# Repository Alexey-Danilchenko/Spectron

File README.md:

# Spectron

Spectron - an open source project for measuring and obtaining digital devices spectral sensitivity curves

Copyright (C) 2014-Now [Alexey Danilchenko](mailto:alexey.danilchenko@gmail.com), [Iliah Borg](mailto:iliah.i.borg@gmail.com)

*This is a work in progress*

# Introduction

This is the second generation of the open source Spectron project.  Initially this was conceived with the goal of constructing an automated device with an aid to accurately measure spectral sensitivity curves for digital camera sensors. The project has a broader use though and can be used to measure spectral sensitivity curves of various light sensitive sensors (not just camera sensors) - for example spectral sensitivity curves of photodiodes.

The main goal however is still to aid measurement of spectral sensitivity of digital cameras sensors and this is what this project and documentation will be aimed towards. For more details on the application of that and the ultimate reasons _why_ please [read this](CameraSRF.md).

The second generation of Spectron board was produced with the more accurate spectral readings in mind, better analogue circuitry to drive Hamamatsu spectrometers and more stable measurement results.

# Concept

The spectral sensitivity measurements of a selected device are fairly simple in principle:

1. broadband light source of high intensity is passed via monochromator
2. monochromator output is fed to the integrating sphere 
3. integrating sphere output is simultaneously captured by target device and measured spectrally
4. steps 1-3 repeated through selected spectral range in discrete steps (5nm steps over 380-720nm range for example)
5. the results of measurements from target device are scaled accodringly to the spectra of the light measured at each step and target spectral sensitivity curves are produced

# Hardware

The hardware for the above concept consists of the light source (LED or pulsed  Xenon), Mini-Chrom MC1-02 monochromator, 2.5" integrating sphere and several distinct components. The Spectrometer component is a hardware driving Hamamatsu [C12666MA](http://www.hamamatsu.com/jp/en/C12666MA.html) or [C12880MA](http://www.hamamatsu.com/jp/en/C12880MA.html) spectrometer sensor to capture spectral readings from the integrating sphere and initiate synchronised readings from target device. The Stepper Motors component is a hardware for automating monochromator operation (esentially converting manually controlled monochromator to scanning monochromator, turning broadband light source into tunable source). The Light Source component is a hardware for controlling broadband light source that provides input for the monochromator.

With the precise intensity control of the LED light source, the whole system is essentially providing tunable monochromatic light source covering the entire visible range.

All hardware component boards use [Particle Photon controllers](https://docs.particle.io/datasheets/wi-fi/photon-datasheet/) at their core to drive the functionality. Overall application control is performed from Windows/Mac application running on a computer operating the boards via Particle or local cloud (the latter is more responsive).

Boards used for all individual components can be of course utilised for standalone projects - see corresponding sections for details.

For more details please refer to individual parts of the project below:

* [Firmware](firmware) - [Particle Photon](https://www.particle.io/products/hardware/photon-wifi-dev-kit) code running on the boards
* [Hardware](hardware) - boards, schematics (Eagle) and BOM 
* [Software](software) - Windows/MacOS X application controlling the overall functionality

# Open Source

This project is open source software and hardware and is released under:

* [GNU General Public License v3](https://www.gnu.org/licenses/gpl-3.0.en.html) for the software parts and 
* [CERN Open Hardware Licence]( http://www.ohwr.org/attachments/735/CERNOHLv1_1.txt) for hardware parts

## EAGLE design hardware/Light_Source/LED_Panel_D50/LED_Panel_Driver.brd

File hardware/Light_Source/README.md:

# Light Sources

The Spectron 2 project uses a wideband light source component as an input to the monochromator. Several light sources with full visible spectrum coverage were evaluated, built and tested for this project. It is important to realize that flat spectrum is not necessary in this application. What is required from a light source is a continuous spectrum, with no gaps. Evaluated light sources all satisfy this criteria. Below is the list of the light sources chosen as a result of this evaluation:

* [LED light source](LEDs) - greater stability and control, this is the preferred light source for Spectron 2 project.
* [Pulsed Xenon short arc light source](Xenon) - great visible spectrum coverage, compact package and point light source best suited to guide light to the monochromator.

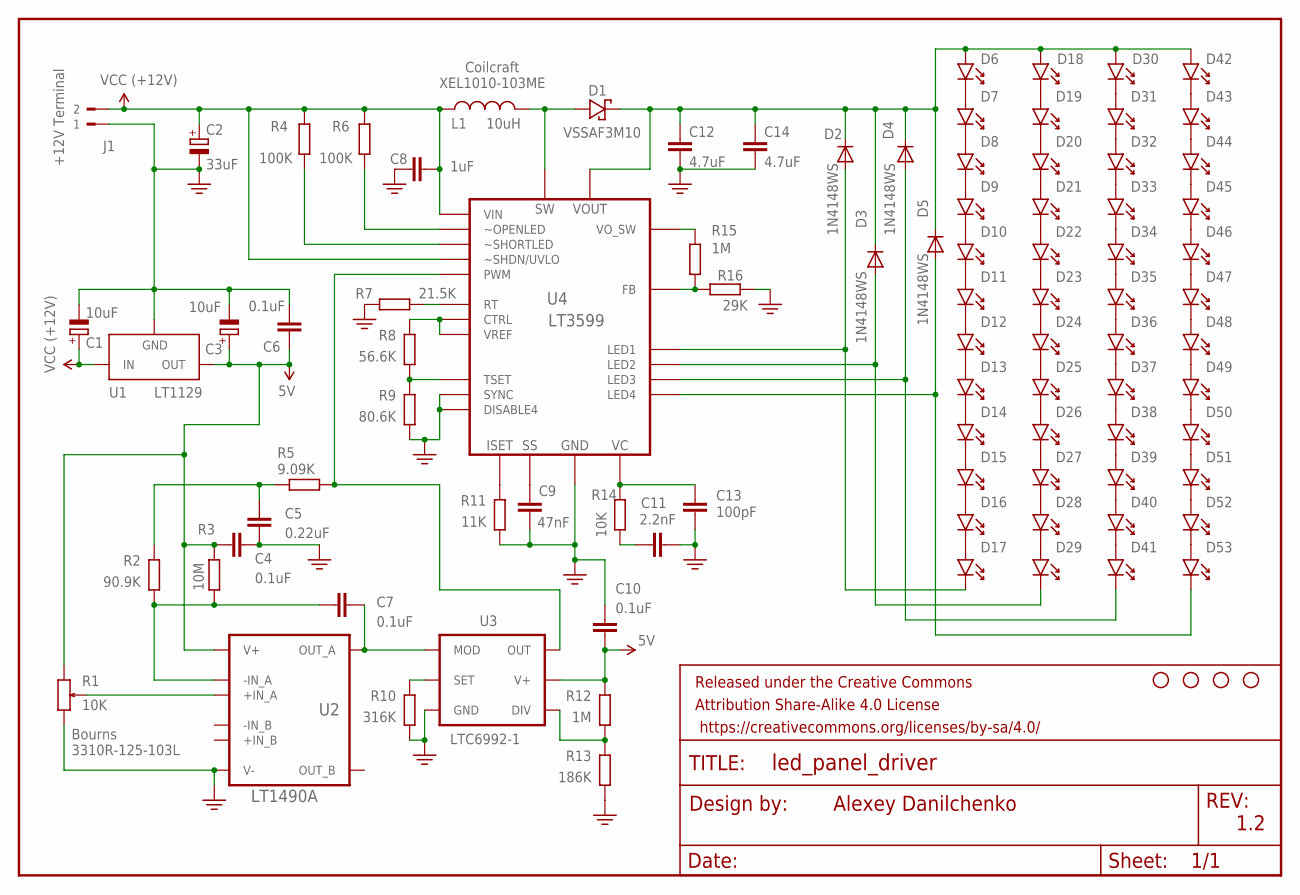
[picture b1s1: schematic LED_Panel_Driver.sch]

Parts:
C1, C3: 10uF; CT7343
C2: 33uF; PANASONIC_E
C4, C6, C7, C10: 0.1uF; C0805
C5: 0.22uF; C0805
C8: 1uF; C0805
C9: 47nF; C0805
C11: 2.2nF; C0805
C12, C14: 4.7uF; C1812
C13: 100pF; C0805
D1: VSSAF3M10; SODFL5226X100N
D2, D3, D4, D5: 1N4148WS; SOD-323F
D6, D7, D8, D9, D10, D11, D12, D13, D14, D15, D16, D17, D18, D19, D20, D21, D22, D23, D24, D25, D26, D27, D28, D29, D30, D31, D32, D33, D34, D35, D36, D37, D38, D39, D40, D41, D42, D43, D44, D45, D46, D47, D48, D49, D50, D51, D52, D53: YUJI_D50
FRAME1: FRAME-LEDGER; CREATIVE_COMMONS
J1: +12V Terminal; WEIDMULLER_PM5.08_2
L1: 10uH; XAL1010
R1: 10K; 3310R125103L
R2: 90.9K; R0805
R3: 10M; R0805
R4, R6: 100K; R0805
R5: 9.09K; R0805
R7: 21.5K; R0805
R8: 56.6K; R0805
R9: 80.6K; R0805
R10: 316K; R0805
R11: 11K; R0805
R12, R15: 1M; R0805
R13: 186K; R0805
R14: 10K; R0805
R16: 29K; R0805
STANDOFF1, STANDOFF2, STANDOFF3, STANDOFF4: STAND-OFF
U1: LT1129; SOT223
U2: LT1490A; SOIC127P600X175-8N
U3: LTC6992-1; SOT95P280X100-6N
U4: LT3599; SOP65P640X120-29N

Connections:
5V: C3.+, C4.2, C6.1, C10.1, R1.3 (CCW), R3.1, R12.1, U1.3 (OUT), U2.8 (V+), U3.5 (V+)
GND: C1.-, C2.-, C3.-, C4.1, C5.1, C6.2, C8.2, C9.2, C10.2, C11.2, C12.2, C13.2, C14.2, J1.1, R1.1 (CW), R7.2, R9.2, R10.2, R11.2, R13.2, R16.1, U1.2 (GND), U1.4 (GND), U2.4 (V-), U3.2 (GND), U4.8 (DISABLE4), U4.19 (SYNC), U4.25 (GND), U4.29 (GND)
unnamed: R8.2, R9.1, U4.17 (TSET)
unnamed: D1.2 (A), L1.2, U4.1 (SW)
unnamed: C12.1, C14.1, D1.1 (K), D2.C, D3.C, D4.C, D5.C, D6.ANODE, D18.ANODE, D30.ANODE, D42.ANODE, U4.2 (VOUT)
unnamed: R15.1, R16.2, U4.16 (FB)
unnamed: D22.CATHODE, D23.ANODE
unnamed: D46.CATHODE, D47.ANODE
unnamed: D2.A, D17.CATHODE, U4.4 (LED1)
unnamed: R8.1, U4.14 (CTRL), U4.24 (VREF)
unnamed: D6.CATHODE, D7.ANODE
unnamed: D3.A, D29.CATHODE, U4.5 (LED2)
unnamed: C9.1, U4.23 (SS)
unnamed: R15.2, U4.3 (VO_SW)
unnamed: R11.1, U4.13 (ISET)
unnamed: R7.1, U4.22 (RT)
unnamed: C13.1, R14.2, U4.15 (VC)
unnamed: C11.1, R14.1
unnamed: R6.2, U4.11 (~OPENLED)
unnamed: R4.2, U4.9 (~SHORTLED)
unnamed: D7.CATHODE, D8.ANODE
unnamed: D8.CATHODE, D9.ANODE
unnamed: D9.CATHODE, D10.ANODE
unnamed: D11.CATHODE, D12.ANODE
unnamed: D12.CATHODE, D13.ANODE
unnamed: D13.CATHODE, D14.ANODE
unnamed: D14.CATHODE, D15.ANODE
unnamed: D15.CATHODE, D16.ANODE
unnamed: D16.CATHODE, D17.ANODE
unnamed: D10.CATHODE, D11.ANODE
unnamed: D18.CATHODE, D19.ANODE
unnamed: D19.CATHODE, D20.ANODE
unnamed: D20.CATHODE, D21.ANODE
unnamed: D21.CATHODE, D22.ANODE
unnamed: D23.CATHODE, D24.ANODE
unnamed: D24.CATHODE, D25.ANODE
unnamed: D25.CATHODE, D26.ANODE
unnamed: D26.CATHODE, D27.ANODE
unnamed: D27.CATHODE, D28.ANODE
unnamed: D28.CATHODE, D29.ANODE
unnamed: D30.CATHODE, D31.ANODE
unnamed: D31.CATHODE, D32.ANODE
unnamed: D32.CATHODE, D33.ANODE
unnamed: D33.CATHODE, D34.ANODE
unnamed: D35.CATHODE, D36.ANODE
unnamed: D36.CATHODE, D37.ANODE
unnamed: D37.CATHODE, D38.ANODE
unnamed: D38.CATHODE, D39.ANODE
unnamed: D39.CATHODE, D40.ANODE
unnamed: D40.CATHODE, D41.ANODE
unnamed: D34.CATHODE, D35.ANODE
unnamed: D42.CATHODE, D43.ANODE
unnamed: D43.CATHODE, D44.ANODE
unnamed: D44.CATHODE, D45.ANODE
unnamed: D45.CATHODE, D46.ANODE
unnamed: D47.CATHODE, D48.ANODE
unnamed: D48.CATHODE, D49.ANODE
unnamed: D49.CATHODE, D50.ANODE
unnamed: D50.CATHODE, D51.ANODE
unnamed: D51.CATHODE, D52.ANODE
unnamed: D52.CATHODE, D53.ANODE
unnamed: D4.A, D41.CATHODE, U4.6 (LED3)
unnamed: D5.A, D53.CATHODE, U4.7 (LED4)
unnamed: R10.1, U3.3 (SET)
unnamed: C7.2, R2.2, R3.2, U2.2 (-IN_A)
unnamed: C7.1, U2.1 (OUT_A), U3.1 (MOD)
unnamed: R5.1, U3.6 (OUT), U4.21 (PWM)
unnamed: R1.2 (WIPER), U2.3 (+IN_A)
unnamed: R12.2, R13.1, U3.4 (DIV)
unnamed: C5.2, R2.1, R5.2
VDD: C1.+, C2.+, C8.1, J1.2, L1.1, R4.1, R6.1, U1.1 (IN), U4.27 (~SHDN/UVLO), U4.28 (VIN)

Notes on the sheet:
1.2
Coilcraft XEL1010-103ME
Alexey Danilchenko
Bourns 3310R-125-103L

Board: 2 copper layers, 94 parts (0 on the bottom side), 71 nets, no tracks yet.

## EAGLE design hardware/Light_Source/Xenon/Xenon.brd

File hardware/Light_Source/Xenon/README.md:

# Xenon Light Source

The Xenon light source component utilises compact pulsed guided short arc Xenon lamp with build in reflector. There are several manufacturers of those lamps - [Hamamatsu](https://www.hamamatsu.com/jp/en/product/light-and-radiation-sources/lamp/xe-f.html) and [Excelitas/Perkin-Elmer](https://www.excelitas.com/product/1100-series-short-arc-xenon-lamps) are well known for their expertise in this area. The setup built and tested for the Spectron 2 utilises [Excelitas/Perkin-Elmer](http://www.excelitas.com/) lamps simply because the off-the-shelf components for them are much easier to find reasonably priced on second hand market (eBay is a great source for them).

This light source construction makes it a very efficient light source for monochromator with very little light loss even without special complicated collimating optics. The metal can lamps from the families referenced above also allow to exceed to a certain degree rated power parameters when lamp is mounted on cooling jackets with sufficient thermal mass. This was tested and fully exploited in firmware accompanying this light sources to provide more efficient light output.

This light source uses [Excelitas/Perkin-Elmer FX-1160 (arc length 1.5mm) or FX-1163 (arc length 3mm) lamps](hhttps://www.excelitas.com/product/1100-series-short-arc-xenon-lamps) widely available new on [eBay at reasonable prices](https://www.ebay.com/itm/Excelitas-FX-1163RT-High-Output-Short-Arc-Xenon-Flashlamp-Flashtube-New-in-Box/122220610629). The lamp also needs a corresponding high voltage (400-1000V) power supply and high voltage trigger module. In our case the [Excelitas/Perkin-Elmer PS-1120 high voltage power supply](http://www.excelitas.com/Downloads/DTS_1100Series_Power_Supplies.pdf) was used together with [Excelitas/Perkin-Elmer FYD‐1150‐B high voltage trigger module](http://www.excelitas.com/Downloads/DTS_1100Series_Trigger_Modules.pdf). The controller board was made to allow to programmatically control the output voltage and triggering rate.

The whole light source component requires external +24V/3A DC power supply to operate.

The pictures below give a clearer idea of the asssembled setup for this component with the lamp triggering:

The controller board uses 0-10V DAC to set output voltage of the high voltage power supply - these power supplies tend to use voltage reference of 1/100th of the desired output to control the output voltage. The board has 2 pin connector to the exnternal +24V DC power supply and 4 pin connector to the high voltage power supply driving the lamp. The output 4 pin connector provides +24V DC, non-isolated logic level trigger signal and 0-10V voltage reference. The [Excelitas/Perkin-Elmer PS-1120 high voltage power supply](http://www.excelitas.com/Downloads/DTS_1100Series_Power_Supplies.pdf) used here has isolated trigger input so no extra isolation is needed. However external trigger signal isolation may be needed (via optocoupler) if a different high voltage power supply is used.

Board schematic is also [available as standalone PDF](Xenon_Light.pdf). Bill of material [is available in Excel format](Xenon_Light_BOM.xlsx).

The following are the board layouts available (generated by OSH Park preview):

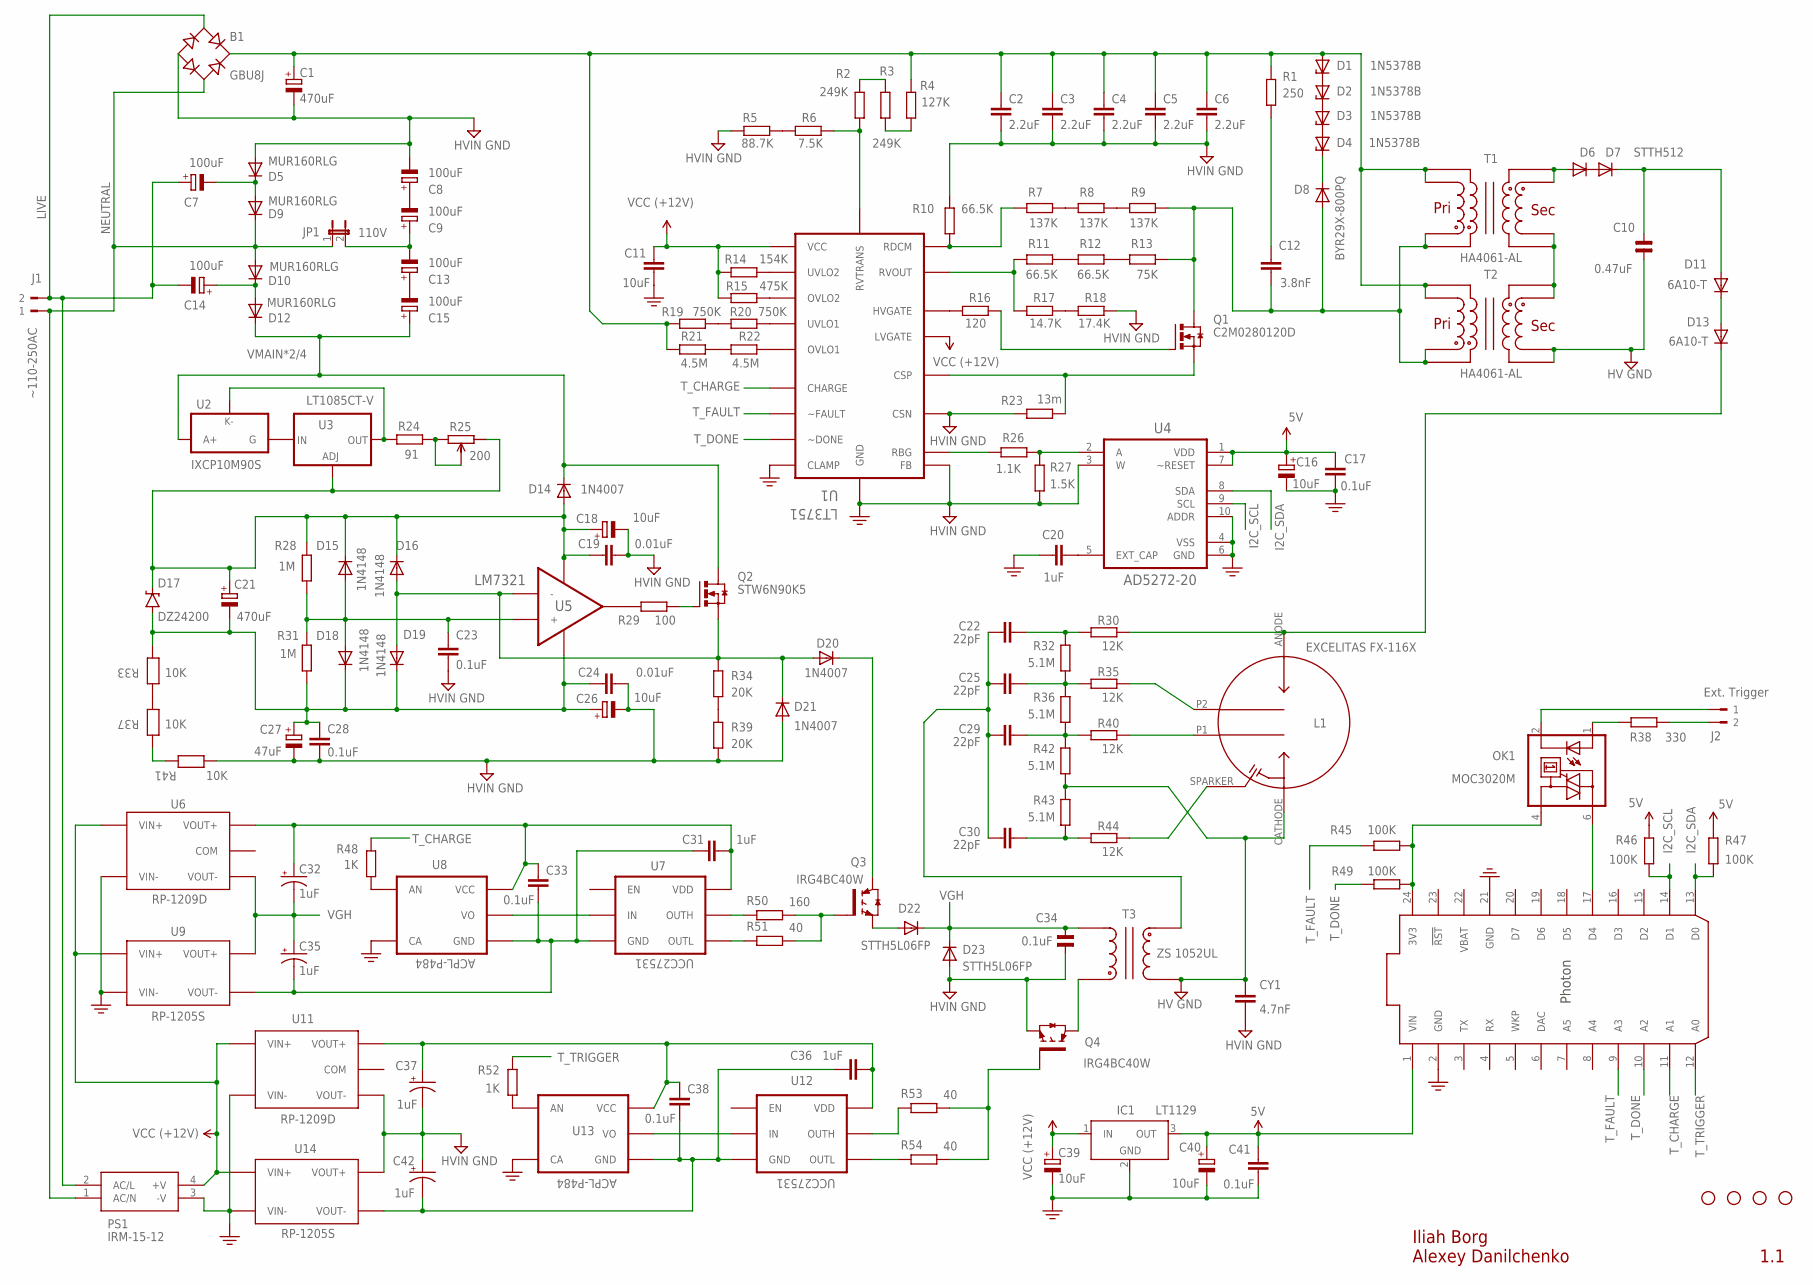
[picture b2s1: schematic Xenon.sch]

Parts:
B1: GBU8J; GBU4
C1: 470uF; EB35D
C2, C3, C4, C5, C6: 2.2uF; C2220K
C7, C8, C9, C13, C14, C15: 100uF; E7,5-18
C10: 0.47uF; R37K5B19
C11: 10uF; C0805
C12: 3.8nF; C0805
C16: 10uF; CT3216
C17, C33, C38, C41: 0.1uF; C0805
C18, C26: 10uF; E5-10,5
C19, C24: 0.01uF; C050-035X075
C20, C31, C36: 1uF; C0805
C21: 470uF; PANASONIC_G
C22, C25, C29, C30: 22pF; C050-030X075
C23, C28: 0.1uF; C050-035X075
C27: 47uF; E5-10,5
C32, C35, C37, C42: 1uF; EIA3216
C34: 0.1uF; R22K5B11
C39, C40: 10uF; CT7343
CY1: 4.7nF; YC10B4
D1, D2, D3, D4: 1N5378B; C1702-15
D5, D9, D10, D12: MUR160RLG; DO41-10
D6: DIODE-TO220V; TO220ACS
D7: STTH512; TO220ACS
D8: BYR29X-800PQ; TO220ACS
D11, D13: 6A10-T; P6-15
D14, D20, D21: 1N4007; DO41-7.6
D15, D16, D18, D19: 1N4148; SOD123
D17: DZ24200; PANASONIC_SMINI2-F5-B
D22, D23: STTH5L06FP; TO220ACS
IC1: LT1129; SOT223
J1: ~110-250AC; WEIDMULLER_PM5.08_2
J2: Ext. Trigger; WEIDMULLER_PM5.08_2
JP1: 110V; JP1
L1: EXCELITAS FX-116X; FX-116X
OK1: MOC3020M; DIL06
PS1: IRM-15-12
Q1: C2M0280120D; TO247BV
Q2: STW6N90K5; TO247BV
Q3, Q4: IRG4BC40W; TO220AV
R1: 250; R1206
R2, R3: 249K; R1206
R4: 127K; R1206
R5: 88.7K; R0805
R6: 7.5K; R0805
R7, R8, R9: 137K; R1206
R10: 66.5K; R0805
R11, R12: 66.5K; R1206
R13: 75K; R1206
R14: 154K; R0805
R15: 475K; R0805
R16: 120; R0805
R17: 14.7K; R0805
R18: 17.4K; R0805
R19, R20: 750K; R1206
R21, R22: 4.5M; R1206
R23: 13m; R1206
R24: 91; R1206
R25: 200; RTRIMT93YA
R26: 1.1K; R0805
R27: 1.5K; R0805
R28, R31: 1M; R1206
R29: 100; R1206
R30, R35, R40, R44: 12K; 0207/10
R32, R36, R42, R43: 5.1M; 0207/10
R33, R37, R41: 10K; RES_WH/NE
R34, R39: 20K; 0309/10
R38: 330; R0805
R45, R46, R47, R49: 100K; R0805
R48, R52: 1K; R1206
R50: 160; R2512
R51, R53, R54: 40; R2512
STANDOFF1, STANDOFF2, STANDOFF3, STANDOFF4: STAND-OFF
T1, T2: HA4061-AL
T3: ZS 1052UL; ZS1052H
U1: LT3751; SOP65P640X120-21N
U2: IXCP10M90S; TO254P482X1016X2386-3P
U3: LT1085CT-V; TO220S
U4: AD5272-20; SOP50P490X110-10N
U5: LM7321; SOT95P280X145-5N
U6, U11: RP-1209D; RECOM-DUAL
U7, U12: UCC27531; SOT95P280X145-6N
U8, U13: ACPL-P484; SOIC6-W
U9, U14: RP-1205S; RECOM-SINGLE
U10: PHOTON_WITH_HEADERS; PHOTON

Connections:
5V: C16.- (+), C17.1, C40.+, C41.1, IC1.3 (OUT), R46.2, R47.2, U4.1 (VDD), U4.7 (~RESET), U10.1 (VIN)
COM: U6.P$6 (COM), U11.P$6 (COM)
GND: C11.2, C16.+ (-), C17.2, C20.1, C39.-, C40.-, C41.2, IC1.2 (GND), IC1.4 (GND), PS1.3 (-V), R27.1, U1.9 (CLAMP), U1.10 (FB), U1.21 (GND), U4.3 (W), U4.4 (VSS), U4.6 (GND), U4.10 (ADDR), U6.P$2 (VIN-), U8.3 (CA), U9.P$2 (VIN-), U10.2 (GND), U10.21 (GND), U11.P$2 (VIN-), U13.3 (CA), U14.P$2 (VIN-)
GND1: C10.2, CY1.1, L1.CATHODE, R42.1, R43.2, T2.P5, T2.P6, T3.P3 (S-S)
GND2: C18.-, C19.2, C23.2, C24.2, C26.-, C27.-, C28.2, C34.2, C37.C (-), C42.A (+), CY1.2, D21.A, D23.A, Q4.3 (E), R5.1, R18.2, R23.1, R39.1, R41.1 (11), U1.11 (CSN), U11.P$5 (VOUT-), U14.P$7 (VOUT+)
I2C_SCL: R46.1, U4.9 (SCL), U10.14 (D1)
I2C_SDA: R47.1, U4.8 (SDA), U10.13 (D0)
IGND1: C31.1, C33.2, C35.C (-), U7.4 (GND), U8.4 (GND), U9.P$5 (VOUT-)
LIVE: B1.AC1, C7.+, C14.-, J1.2, PS1.2 (AC/L)
unnamed: C10.1, D7.C, D11.A
unnamed: R5.2, R6.1
unnamed: R50.1, U7.6 (OUTH)
unnamed: Q3.1 (G), R50.2, R51.2
unnamed: D13.C, L1.ANODE, R30.2
unnamed: C12.2, D8.A, Q1.D, R9.2, R13.2, T1.P1, T1.P2, T2.P1, T2.P2
unnamed: R51.1, U7.5 (OUTL)
unnamed: R54.1, U12.5 (OUTL)
unnamed: T1.P5, T1.P6, T2.P7, T2.P8
unnamed: D6.A, T1.P7, T1.P8
unnamed: OK1.4 (A1), R45.1, R49.1, U10.24 (3V3)
unnamed: R53.1, U12.6 (OUTH)
unnamed: Q4.1 (G), R53.2, R54.2
unnamed: U2.1 (G), U3.3 (IN)
unnamed: L1.SPARKER, R44.2
unnamed: U12.2 (IN), U13.5 (VO)
unnamed: D22.A, Q3.3 (E)
unnamed: R52.1, U13.1 (AN)
unnamed: U7.2 (IN), U8.5 (VO)
unnamed: C22.1, C25.1, C29.1, C30.1, T3.P4 (S-P)
unnamed: C36.1, C38.2, C42.C (-), U12.4 (GND), U13.4 (GND), U14.P$5 (VOUT-)
unnamed: C30.2, R43.1, R44.1
unnamed: C29.2, R36.1, R40.1, R42.2
unnamed: C25.2, R32.1, R35.1, R36.2
unnamed: C22.2, R30.1, R32.2
unnamed: L1.P2, R35.2
unnamed: C31.2, C32.A (+), C33.1, U6.P$7 (VOUT+), U7.3 (VDD), U8.6 (VCC)
unnamed: L1.P1, R40.2
unnamed: D6.C, D7.A
unnamed: OK1.1 (A), R38.2
unnamed: OK1.6 (A2), U10.17 (D4)
unnamed: J2.2, R38.1
unnamed: J2.1, OK1.2 (C)
unnamed: C36.2, C37.A (+), C38.1, U11.P$7 (VOUT+), U12.3 (VDD), U13.6 (VCC)
unnamed: Q4.2 (C), T3.P2 (P-P)
unnamed: R48.1, U8.1 (AN)
unnamed: R24.1, U2.3 (K-), U3.2 (OUT)
unnamed: R33.2 (22), R37.1 (11)
unnamed: R37.2 (22), R41.2 (22)
unnamed: C21.-, C24.1, C26.+, C27.+, C28.1, D17.A, D18.C, D19.C, R31.1, R33.1 (11), U5.2 (-VS)
unnamed: C7.-, D5.C, D9.A
unnamed: R24.2, R25.2 (S), R25.3 (A)
unnamed: C23.1, D15.A, D18.A, R28.1, R31.2, U5.3 (+)
unnamed: D16.A, D19.A, D20.A, D21.C, Q2.S, R34.2, U5.4 (-)
unnamed: R3.1, R4.1
unnamed: R34.1, R39.2
unnamed: R29.1, U5.1 (VOUT)
unnamed: Q2.G, R29.2
unnamed: R7.2, R8.1
unnamed: R20.2, U1.2 (UVLO1)
unnamed: R19.2, R20.1
unnamed: R22.2, U1.3 (OVLO1)
unnamed: R21.2, R22.1
unnamed: B1.+, C1.+, C2.1, C3.1, C4.1, C5.1, C6.1, D1.A, R1.2, R4.2, R19.1, R21.1, T1.P11, T1.P12, T2.P11, T2.P12
unnamed: R14.2, U1.4 (UVLO2)
unnamed: R15.2, U1.5 (OVLO2)
unnamed: R2.2, R3.2
unnamed: R2.1, R6.2, U1.1 (RVTRANS)
unnamed: Q1.S, R23.2, U1.12 (CSP)
unnamed: R17.2, R18.1
unnamed: R16.1, U1.15 (HVGATE)
unnamed: Q1.G, R16.2
unnamed: R7.1, R10.1, U1.20 (RDCM)
unnamed: R8.2, R9.1
unnamed: R26.1, R27.2, U4.2 (A)
unnamed: R11.1, R17.1, U1.18 (RVOUT)
unnamed: R11.2, R12.1
unnamed: R12.2, R13.1
unnamed: C13.+, C15.-
unnamed: C20.2, U4.5 (EXT_CAP)
unnamed: R26.2, U1.16 (RBG)
unnamed: C18.+, C19.1, C21.+, D14.A, D15.C, D16.C, D17.C, R25.1 (E), R28.2, U3.1 (ADJ), U5.5 (+VS)
unnamed: C14.+, D10.C, D12.A
unnamed: C9.+, C13.-, JP1.2
unnamed: C8.+, C9.-
unnamed: D11.C, D13.A
unnamed: D1.C, D2.A
unnamed: D2.C, D3.A
unnamed: D3.C, D4.A
unnamed: D4.C, D8.C
unnamed: C12.1, R1.1
NEUTRAL: B1.AC2, D9.C, D10.A, J1.1, JP1.1, PS1.1 (AC/N)
TR_GND: B1.-, C1.-, C2.2, C3.2, C4.2, C5.2, C6.2, C8.-, D5.A, R10.2
T_CHARGE: R48.2, U1.8 (CHARGE), U10.11 (A1)
T_DONE: R49.2, U1.7 (~DONE), U10.10 (A2)
T_FAULT: R45.2, U1.6 (~FAULT), U10.9 (A3)
T_TRIGGER: R52.2, U10.12 (A0)
VBAT: U10.22 (VBAT)
VDD: C11.1, C39.+, IC1.1 (IN), PS1.4 (+V), R14.1, R15.1, U1.13 (VCC), U1.14 (LVGATE), U6.P$1 (VIN+), U9.P$1 (VIN+), U11.P$1 (VIN+), U14.P$1 (VIN+)
VGH: C32.C (-), C34.1, C35.A (+), D22.C, D23.C, T3.P1 (P-S), U6.P$5 (VOUT-), U9.P$7 (VOUT+)
VMAIN*2/4: C15.+, D12.C, D14.C, Q2.D, U2.2 (A+)
VTRG: D20.C, Q3.2 (C)

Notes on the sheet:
1.1
Iliah Borg Alexey Danilchenko

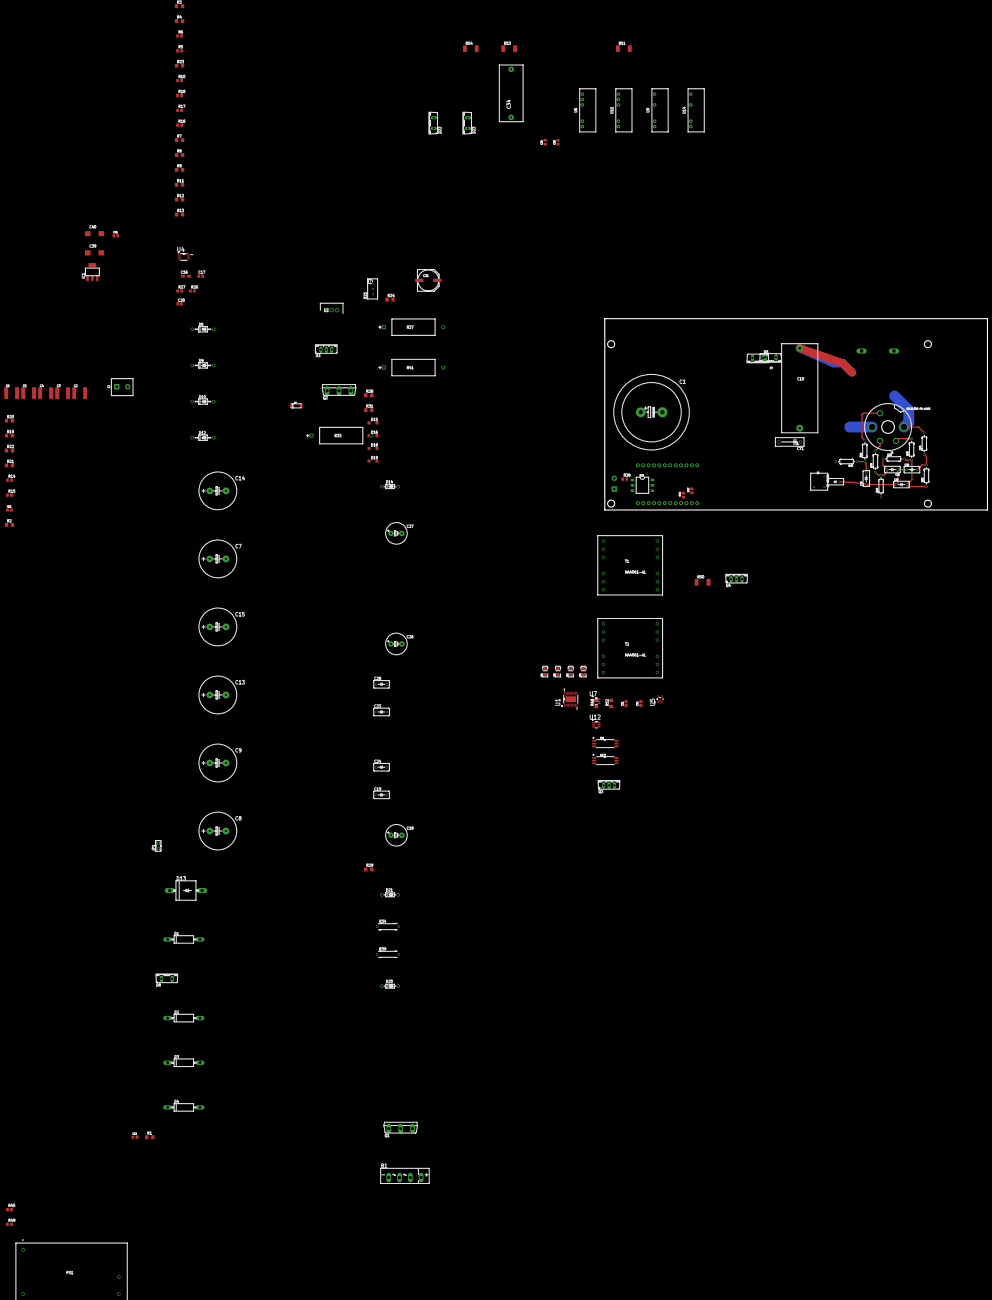
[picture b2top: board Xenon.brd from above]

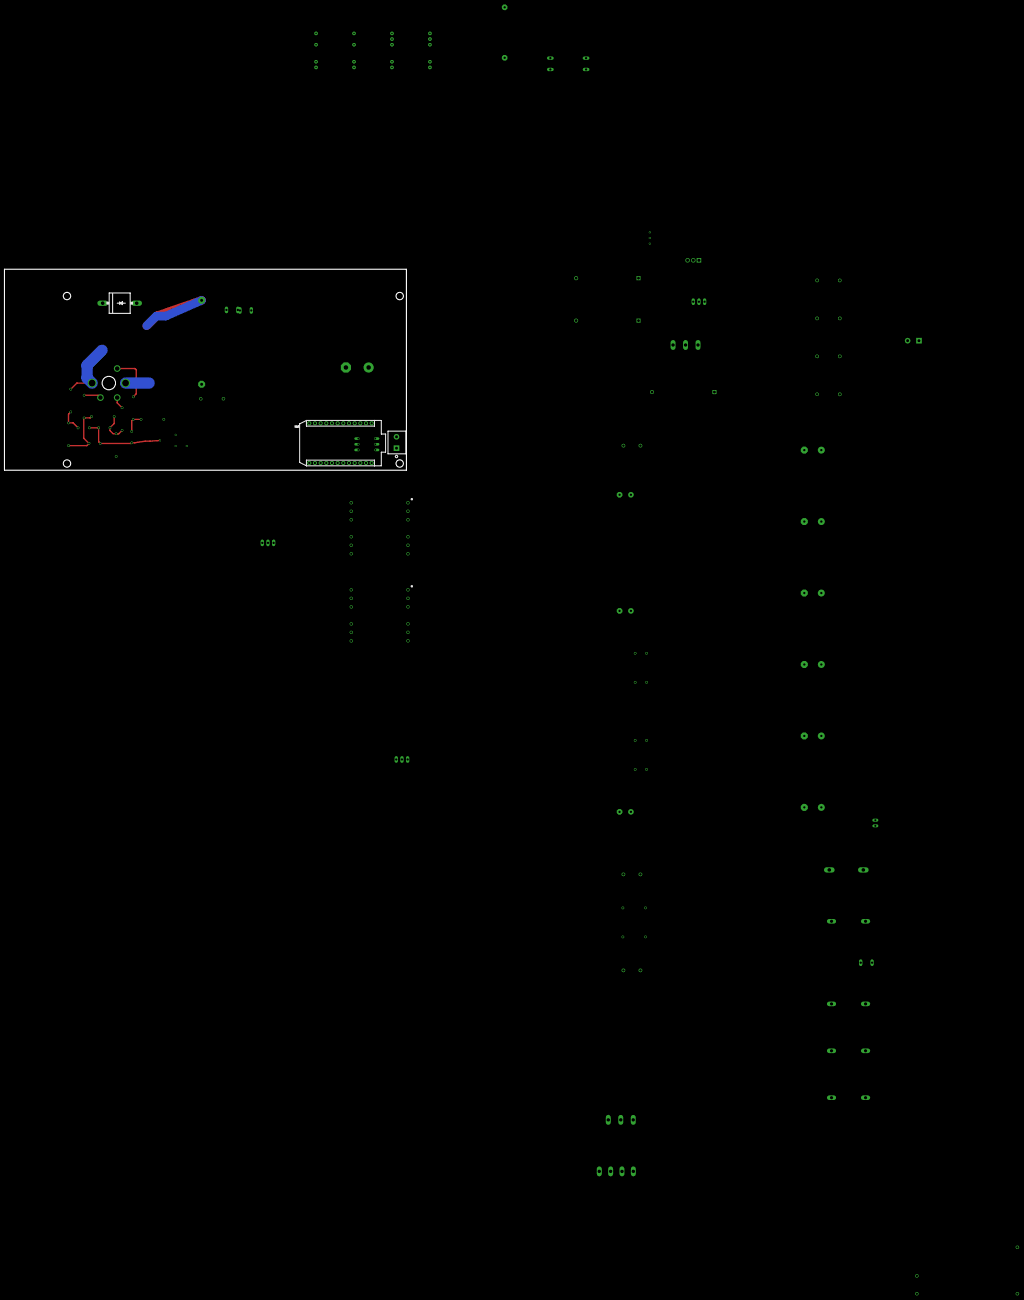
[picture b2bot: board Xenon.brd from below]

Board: 2 copper layers, 180.0 x 90.0 mm, 153 parts (3 on the bottom side), 100 nets.

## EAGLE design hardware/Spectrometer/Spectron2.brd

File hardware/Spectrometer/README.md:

# Spectron 2 - Spectrometer controlling board

This is the main board that is responsible for spectral measurements. The board has analogue circuitry to drive Hamamatsu [C12666MA](http://www.hamamatsu.com/jp/en/C12666MA.html) or [C12880MA](http://www.hamamatsu.com/jp/en/C12880MA.html) micro spectrometers and interfaces to trigger external devices or light sources simultaneously with measurements. The board requires +5V DC power supply to operate.

The board also has a multipurpouse interface connector suitable for custom adaptations that provides access to SPI, I2C and generic digital/analogue pins on Particle Photon. This project does not make use of this connector but example firmware is provided to demonstrate its use with Adafruit 2.2" 18-bit TFT LCD module.

Board schematic is also [available as standalone PDF](Spectron2.pdf). Bill of material [is available in Excel format](Spectron2_BOM.xlsx).

The Hamamatsu C12666MA and C12880MA spectrometers have different hardware pinout and for that reason they are attached to this board through their own little sensor boards. Those were designed with my specific attachment to integrating sphere in mind and come in both vertical and horisontal layouts (they differ in a way the main board attaches to the sensor board).

The following are the board layouts available (generated by OSH Park preview):

* Spectron 2 - front and back

* Hamamatsu C12666 sensor board (horisontal) - front and back

* Hamamatsu C12666 sensor board (vertical) - front and back

* Hamamatsu C12880 sensor board (horisontal) - front and back

* Hamamatsu C12880 sensor board (vertical) - front and back

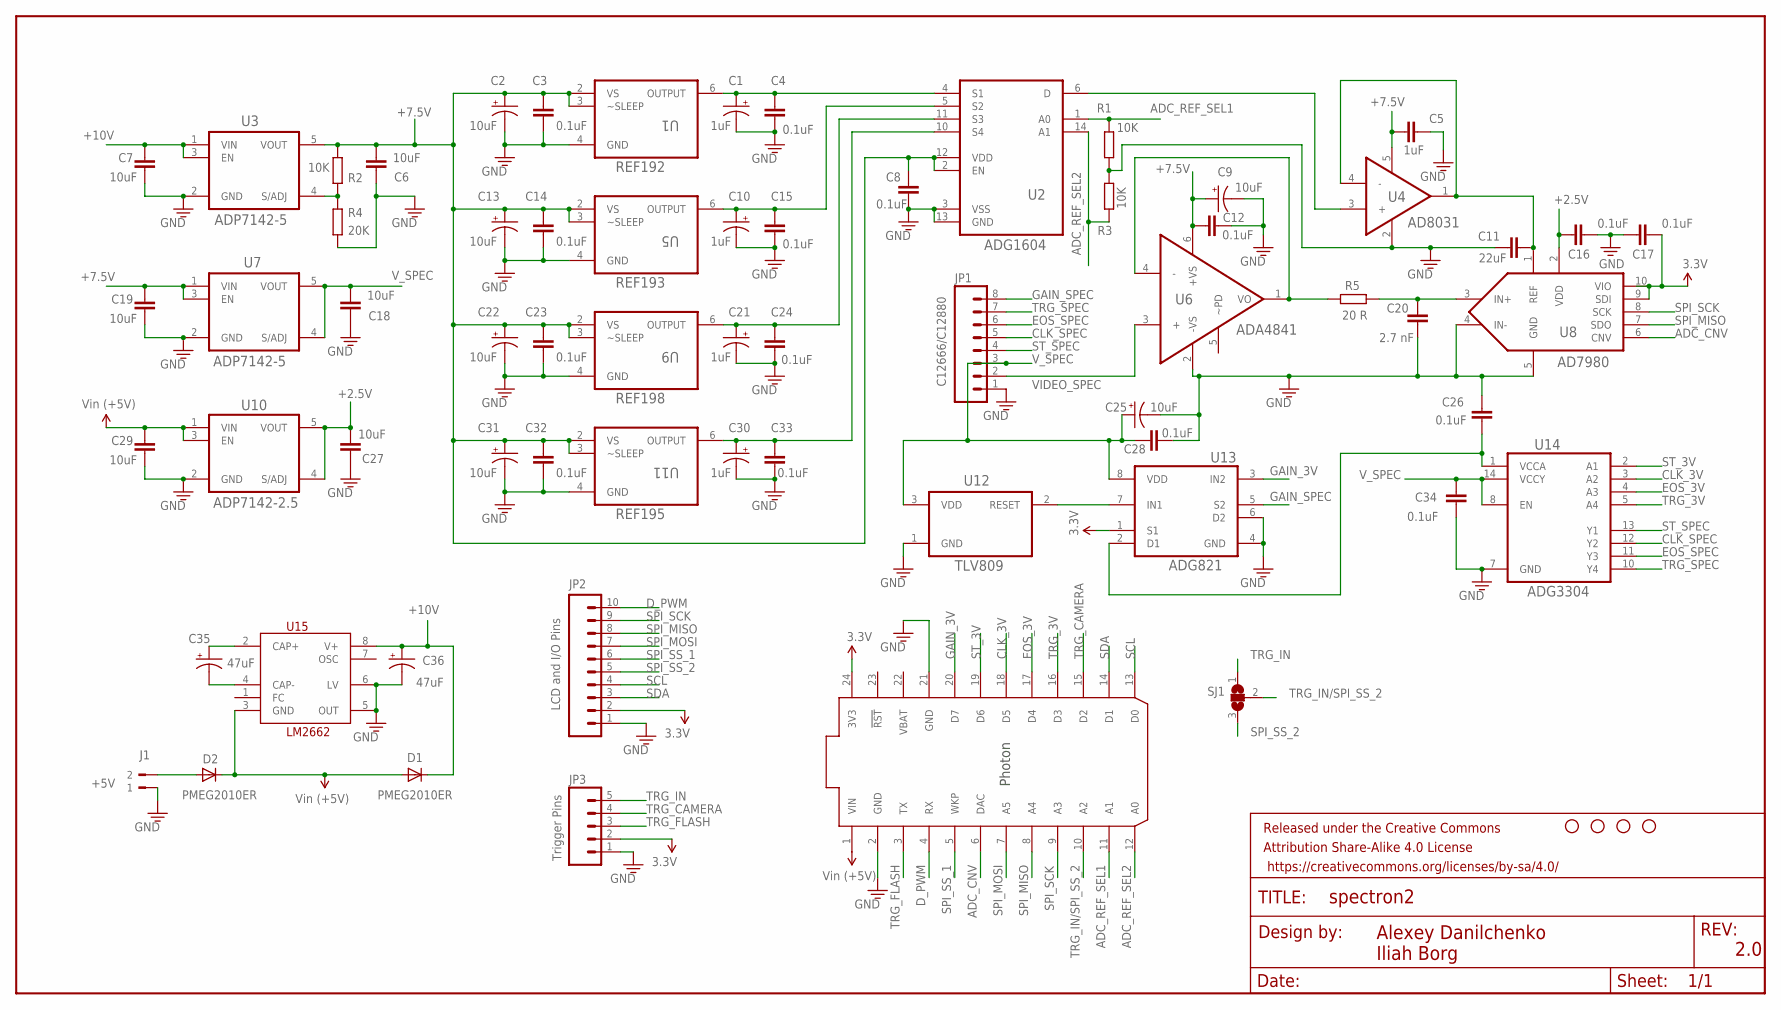
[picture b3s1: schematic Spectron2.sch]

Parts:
C1, C10, C21, C30: 1uF; EIA3216
C2, C9, C13, C22, C25, C31: 10uF; EIA3216
C3, C4, C8, C12, C14, C15, C16, C17, C23, C24, C26, C28, C32, C33, C34: 0.1uF; C0805
C5: 1uF; C0805
C6, C7, C18, C19, C27, C29: 10uF; C0805
C11: 22uF; 1206
C20: 2.7 nF; C0805
C35, C36: 47uF; CT7343
D1, D2: PMEG2010ER; SOD123
FRAME1: FRAME-LEDGER; CREATIVE_COMMONS
J1: +5V; WEIDMULLER_PM5.08_2
JP1: C12666/C12880; 1X08
JP2: LCD and I/O Pins; 1X10
JP3: Trigger Pins; 1X05
R1, R2, R3: 10K; R0805
R4: 20K; R0805
R5: 20 R; R0805
SJ1: SJ2W; SJ_2
STANDOFF1, STANDOFF2, STANDOFF3, STANDOFF4: STAND-OFF
U1: REF192; SOIC127P600X175-8N
U2: ADG1604; SOP65P640X120-14N
U3, U7: ADP7142-5; SOT95P280X145-5N
U4: AD8031; SOT95P280X145-5N
U5: REF193; SOIC127P600X175-8N
U6: ADA4841; SOT95P280X145-6N
U8: AD7980; SOP50P490X110-10N
U9: REF198; SOIC127P600X175-8N
U10: ADP7142-2.5; SOT95P280X145-5N
U11: REF195; SOIC127P600X175-8N
U12: TLV809; SOT95P237X112-3N
U13: ADG821; SOP65P490X110-8N
U14: ADG3304; SOP65P640X120-14N
U15: LM2662; SOIC8
U16: PHOTON_WITH_HEADERS; PHOTON

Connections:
3.3V: C17.2, JP2.2, JP3.2, U8.9 (SDI), U8.10 (VIO), U13.1 (S1), U16.24 (3V3)
+2.5V: C16.1, C27.1, U8.2 (VDD), U10.4 (S/ADJ), U10.5 (VOUT)
+7.5V: C2.A (+), C3.2, C5.2, C6.1, C8.2, C9.A (+), C12.2, C13.A (+), C14.2, C19.2, C22.A (+), C23.2, C31.A (+), C32.2, R2.1, U1.2 (VS), U1.3 (~SLEEP), U2.2 (EN), U2.12 (VDD), U3.5 (VOUT), U4.5 (+VS), U5.2 (VS), U5.3 (~SLEEP), U6.6 (+VS), U7.1 (VIN), U7.3 (EN), U9.2 (VS), U9.3 (~SLEEP), U11.2 (VS), U11.3 (~SLEEP)
+10V: C7.2, C36.+, D1.C, U3.1 (VIN), U3.3 (EN), U15.8 (V+)
ADC_CNV: U8.6 (CNV), U16.6 (DAC)
ADC_REF_SEL1: R1.1, U2.1 (A0), U16.11 (A1)
ADC_REF_SEL2: R3.2, U2.14 (A1), U16.12 (A0)
CLK_3V: U14.3 (A2), U16.18 (D5)
CLK_SPEC: JP1.5, U14.12 (Y2)
D_PWM: JP2.10, U16.4 (RX)
EOS_3V: U14.4 (A3), U16.17 (D4)
EOS_SPEC: JP1.6, U14.11 (Y3)
GAIN_3V: U13.3 (IN2), U16.20 (D7)
GAIN_SPEC: JP1.8, U13.5 (S2)
GND: C1.C (-), C2.C (-), C3.1, C4.1, C5.1, C6.2, C7.1, C8.1, C9.C (-), C10.C (-), C11.1, C12.1, C13.C (-), C14.1, C15.1, C16.2, C17.1, C18.2, C19.1, C20.1, C21.C (-), C22.C (-), C23.1, C24.1, C25.C (-), C26.2, C27.2, C28.1, C29.1, C30.C (-), C31.C (-), C32.1, C33.1, C34.1, C36.-, J1.1, JP1.1, JP2.1, JP3.1, R1.2, R3.1, R4.2, U1.4 (GND), U2.3 (VSS), U2.13 (GND), U3.2 (GND), U4.2 (-VS), U5.4 (GND), U6.2 (-VS), U7.2 (GND), U8.4 (IN-), U8.5 (GND), U9.4 (GND), U10.2 (GND), U11.4 (GND), U12.1 (GND), U13.4 (GND), U13.6 (D2), U14.7 (GND), U15.5 (OUT), U15.6 (LV), U16.2 (GND), U16.21 (GND)
unnamed: R2.2, R4.1, U3.4 (S/ADJ)
unnamed: C11.2, U4.1 (VOUT), U4.4 (-), U8.1 (REF)
unnamed: C21.A (+), C24.2, U2.11 (S3), U9.6 (OUTPUT)
unnamed: R5.2, U6.1 (VO), U6.4 (-)
unnamed: U12.2 (RESET), U13.7 (IN1)
unnamed: C1.A (+), C4.2, U1.6 (OUTPUT), U2.4 (S1)
unnamed: U2.6 (D), U4.3 (+)
unnamed: C10.A (+), C15.2, U2.5 (S2), U5.6 (OUTPUT)
unnamed: C30.A (+), C33.2, U2.10 (S4), U11.6 (OUTPUT)
unnamed: D2.A, J1.2
unnamed: C20.2, R5.1, U8.3 (IN+)
unnamed: C35.-, U15.4 (CAP-)
unnamed: C35.+, U15.2 (CAP+)
unnamed: C26.1, U13.2 (D1), U14.1 (VCCA)
SCL: JP2.4, U16.13 (D0)
SDA: JP2.3, U16.14 (D1)
SPI_MISO: JP2.8, U8.7 (SDO), U16.8 (A4)
SPI_MOSI: JP2.7, U16.7 (A5)
SPI_SCK: JP2.9, U8.8 (SCK), U16.9 (A3)
SPI_SS_1: JP2.6, U16.5 (WKP)
SPI_SS_2: JP2.5, SJ1.3
ST_3V: U14.2 (A1), U16.19 (D6)
ST_SPEC: JP1.4, U14.13 (Y1)
TRG_3V: U14.5 (A4), U16.16 (D3)
TRG_CAMERA: JP3.4, U16.15 (D2)
TRG_FLASH: JP3.3, U16.3 (TX)
TRG_IN: JP3.5, SJ1.1
TRG_IN/SPI_SS_2: SJ1.2, U16.10 (A2)
TRG_SPEC: JP1.7, U14.10 (Y4)
VBAT: U16.22 (VBAT)
VIDEO_SPEC: JP1.2, U6.3 (+)
VIN: C29.2, D1.A, D2.C, U10.1 (VIN), U10.3 (EN), U15.3 (GND), U16.1 (VIN)
V_SPEC: C18.1, C25.A (+), C28.2, C34.2, JP1.3, U7.4 (S/ADJ), U7.5 (VOUT), U12.3 (VDD), U13.8 (VDD), U14.8 (EN), U14.14 (VCCY)

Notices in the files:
firmware/Motors/DRV8884.cpp:
Copyright 2017-2018 Alexey Danilchenko, Iliah Borg
parts and their libraries:
SparkFun-Aesthetics: Licensing: Creative Commons ShareAlike 4.0 International - https://creativecommons.org/licenses/by-sa/4.0
LEDS: Released under the Creative Commons
LEDS: https://creativecommons.org/licenses/by-sa/4.0
